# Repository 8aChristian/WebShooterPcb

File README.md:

# 🕸️ WebShooter — Wearable Actuation & High-Response Sensing PCB

<div align="center">

</div>

---

## 1. 🎯 Objective

**WebShooter** is a compact, high-reliability wearable controller PCB designed for rapid biosignal/force acquisition, low-latency electronic valve actuation, and external brushless motor ESC control.

Built around the **ESP32-C3 SuperMini** (RISC-V 32-bit architecture), the system is engineered to withstand intense inductive transients and severe electromagnetic interference (EMI) from high-power loads while providing precision analog readings from a Force Sensing Resistor (FSR).

> [!NOTE]
> **Key Capabilities:**
> - **Fast Response Time:** Sub-millisecond analog force detection via hardware RC filtering.
> - **Inductive Load Immunity:** High-speed Schottky flyback suppression and isolated ground return loops.
> - **Modular Design:** Socketed MCU mounting for effortless replacement and maintenance.

---

## 2. 🏗️ System Architecture

```mermaid
graph LR
    subgraph Power_Stage ["Power and Regulation Stage"]
        BATT["Battery LiPo 2S (7.4V - 8.4V)"] -->|J_BATT| LDO["AMS1117-3.3 LDO"]
        LDO -->|"10uF In + 22uF Out"| V33["3.3V DC Clean Rail"]
    end

    subgraph MCU_Stage ["Control Unit ESP32-C3 SuperMini"]
        V33 --> MCU["ESP32-C3 (RISC-V @ 160MHz)"]
        MCU -->|GPIO8| LED["Status Indicator LED"]
    end

    subgraph Sensor_Stage ["Analog Force Sensing"]
        V33 --> FSR_DIV["10k Ohm Reference Divider"]
        FSR["FSR402 Sensor"] --> FSR_DIV
        FSR_DIV -->|"100nF LowPass + 1k Ohm Prot"| ADC["GPIO0 (ADC1_CH0)"]
    end

    subgraph Actuation_Stage ["Power Actuation and Motor Drive"]
        MCU -->|GPIO7 Logic Gate| DRV["AO3400A N-MOSFET (30V / 5.7A)"]
        BATT -->|7.4V Heavy Rail| SOL["Solenoid Valve (Inductive Load)"]
        DRV -->|"Drain + SS14 Flyback Diode"| SOL
        MCU -->|"GPIO6 PWM - 100 Ohm Damper"| ESC["External ESC (SpeedX2 1404 BLDC)"]
        BATT -.->|"Direct Battery Wiring"| ESC
    end
```

- **MCU:** ESP32-C3 SuperMini (RISC-V 32-bit single-core @ 160 MHz, 400 KB SRAM, 4 MB Flash, Wi-Fi + BLE 5).
- **Analog Front-End (AFE):** Precision voltage divider with a 100 nF ceramic low-pass filter ($f_c \approx 159\text{ Hz}$) and $1\text{ k}\Omega$ series current limiter.
- **Power Management & Drive:** AMS1117-3.3 LDO regulator with dual ceramic filtering; logic-level AO3400A N-MOSFET with SS14 Schottky flyback protection; isolated ESC PWM signaling.

---

## 3. 🔬 Component Selection & Design Decisions

| Subsystem | Component Selected | Engineering Rationale & Justification |
| :--- | :--- | :--- |
| **Microcontroller** | **ESP32-C3 SuperMini** | Ultra-compact footprint ($22.5 \times 18\text{ mm}$), native 12-bit ADC, hardware PWM timers, low power consumption, and integrated 2.4 GHz Wi-Fi/BLE for wireless telemetry. Mounted on **2.54 mm female headers** (`J1`, `J2`) to prevent module thermal stress during assembly and allow instant replacement. |
| **Solenoid Driver** | **AO3400A N-MOSFET** (SOT-23) | Ultra-low on-resistance ($R_{DS(on)} < 33\text{ m}\Omega$ @ $V_{GS} = 2.5\text{V}$), fully saturated with the ESP32's 3.3V logic. At $I = 0.8\text{A}$, power dissipation is negligible ($P_{cond} \approx 21.1\text{ mW}$), eliminating the need for bulky heatsinks. |
| **Flyback Protection** | **SS14 Schottky Diode** (SOD-123) | Placed directly in antiparallel across the solenoid terminals. Ultrafast reverse recovery ($t_{rr} < 10\text{ ns}$) and $0.5\text{V}$ forward drop clamp inductive voltage spikes ($V = -L \frac{di}{dt}$) to protect the MOSFET drain and ground plane from EMI bursts. |
| **Voltage Regulator** | **AMS1117-3.3** (SOT-223) | Handles 7.4V–8.4V LiPo 2S input with 1A current capacity. SOT-223 tab is tied to the output plane for optimal thermal dissipation. Paired with $10\,\mu\text{F}$ input and $22\,\mu\text{F}$ output ceramic X7R capacitors. |
| **Force Sensor AFE** | **FSR402 Divider + RC Filter** | Converts pressure ($0.2\text{ N} - 20\text{ N}$) into a clean $0.03\text{V} - 3.0\text{V}$ voltage curve. The hardware RC filter ($10\text{ k}\Omega \parallel 100\text{ nF}$) removes mechanical contact bounce and EMI from nearby motor switching. |
| **Motor & ESC Isolation** | **Signal-Only PWM Interface** | Heavy motor currents (up to 15A from the SpeedX2 1404 BLDC) are powered **directly from the battery pack wiring harness**. Only the PWM control line and reference ground pass through the PCB, preventing ground bounce and motor hash from corrupting the ADC. |

---

## 4. 📐 Schematic Overview

<div align="center">
  
  <p><em>Full vector PDF schematic is available in the <a href="schematic/WebShooter_Schematic.pdf"><code>/schematic</code></a> folder.</em></p>
</div>

> [!TIP]
> **Complete Schematic Documentation:**
> - 📄 **PDF Format:** [`schematic/WebShooter_Schematic.pdf`](schematic/WebShooter_Schematic.pdf)
> - 🎨 **Vector SVG:** [`schematic/WebShooter_Schematic.svg/`](schematic/WebShooter_Schematic.svg/)
> - 💻 **KiCad Source:** [`pcb/WebShooter.kicad_sch`](pcb/WebShooter.kicad_sch)

---

## 5. 🖨️ PCB Layout & Routing Strategy

<div align="center">

| Top Layer 2D Layout (F.Cu) | Bottom Layer 2D Layout (B.Cu) |
| :---: | :---: |
|  |  |

| 3D Render - Top Side | 3D Render - Bottom Side |
| :---: | :---: |
|  |  |

</div>

### 🛠️ Layer Stackup & Dimensions
- **Layer Count:** 2-Layer FR4 ($1.6\text{ mm}$ board thickness, $1\text{ oz} / 35\,\mu\text{m}$ copper weight).
- **Board Dimensions:** $38.0\text{ mm} \times 38.0\text{ mm}$ with $2.0\text{ mm}$ corner radius fillets (Ultra-compact wearable standard).
- **Mounting Hole Grid:** 4x M2 mounting holes on a $31.0 \times 31.0\text{ mm}$ pattern ($3.5\text{ mm}$ from board edges).

### 📐 Routing Guidelines & DFM Standards Applied
1. **Strict 45° Mitered Routing (Zero 90° Corners):**
   - All track bends utilize **45-degree chamfers** or smooth radii.
   - *Why:* Eliminates **acid traps** during chemical etching in fab, avoids acute impedance steps, and prevents solder mask delamination.
2. **Edge Pullback Clearance ($\ge 1.0\text{ mm}$):**
   - All copper tracks, vias, and copper pour zones maintain at least **$1.0\text{ mm}$ of clearance** from the `Edge_Cuts` perimeter.
   - *Why:* Prevents copper shearing, burrs, and shorts during CNC V-scoring and board routing.
3. **Trace Width Dimensioning (IPC-2152):**
   - **Power & Solenoid Traces:** $1.0\text{ mm} - 1.2\text{ mm}$ (Handles up to $3\text{A}$ continuous with $\Delta T < 10^\circ\text{C}$).
   - **3.3V Power Distribution:** $0.8\text{ mm}$.
   - **Digital PWM & Analog Signals:** $0.35\text{ mm} - 0.40\text{ mm}$.
4. **Dual Continuous Ground Planes:**
   - Both `F.Cu` and `B.Cu` feature unbroken GND copper zones connected through thermal reliefs (`ZONE_CONNECTION_THERMAL`) on all through-hole and SMD ground pins.

---

## 6. ✅ DRC & Quality Verification

Automated Design Rule Check (DRC) executed via `kicad-cli`:

```text
** KiCad 10 Design Rule Check Report **
Project: WebShooter.kicad_pcb
Date: 2026-08-20

[+] Status: PASSED
[+] Total DRC Violations: 0
[+] Unconnected Elements: 0
[+] Footprint Courtyard Overlaps: 0
[+] Solder Mask Bridges: 0
[+] Silk Over Exposure: 0
```

> [!IMPORTANT]
> The full verification report is saved in [`pcb/WebShooter-drc.rpt`](pcb/WebShooter-drc.rpt).

---

## 7. 🧊 3D Model & Mechanical Integration

- **PCB 3D Model:** Ready-to-import STEP file:
  - 📁 [`3d-model/WebShooter.step`](3d-model/WebShooter.step)
- **Wearable Case / Enclosure (CAD):** Parametric wrist case model for 3D printing:
  - 📦 [`3d-model/WEBSHOOTERCASEFINAL.f3d`](3d-model/WEBSHOOTERCASEFINAL.f3d) (Autodesk Fusion 360 source archive)
- **Mechanical Mounting:** 4x M2 mounting holes on a $31.0 \times 31.0\text{ mm}$ square grid ($3.5\text{ mm}$ edge offset), designed to mate directly with the 3D-printed enclosure standoffs.

---

## 8. 🏭 Manufacturing & Assembly (JLCPCB / PCBWay Ready)

| Asset | Location / File | Purpose |
| :--- | :--- | :--- |
| **Gerber Files (ZIP)** | [`gerbers/WebShooter_Gerbers_JLCPCB.zip`](gerbers/WebShooter_Gerbers_JLCPCB.zip) | One-click drag-and-drop file for instant online quoting |
| **Individual Gerbers** | [`gerbers/`](gerbers/) | Standard RS-274X layers (`.gtl`, `.gbl`, `.gts`, `.gbs`, `.gto`, `.gm1`...) |
| **Drill File** | [`gerbers/WebShooter.drl`](gerbers/WebShooter.drl) | Excellon CNC drill specifications |
| **BOM (CSV)** | [`bom/WebShooter_BOM.csv`](bom/WebShooter_BOM.csv) | Component spreadsheet with LCSC Part Numbers |
| **BOM (Markdown)** | [`bom/WebShooter_BOM.md`](bom/WebShooter_BOM.md) | Formatted Bill of Materials table |
| **Case CAD (F3D)** | [`3d-model/WEBSHOOTERCASEFINAL.f3d`](3d-model/WEBSHOOTERCASEFINAL.f3d) | 3D-printable parametric enclosure design |

### 🚀 Production Parameters Recommended
- **Base Material:** FR-4 (Tg 130–140°C).
- **PCB Thickness:** 1.6 mm.
- **Copper Weight:** 1 oz ($35\,\mu\text{m}$).
- **Surface Finish:** HASL Lead-Free or ENIG (Electroless Nickel Immersion Gold).
- **Solder Mask:** Matte Black / Blue / Green.
- **Silkscreen:** High-contrast White.

---

## 📜 License

This project is licensed under the [MIT License](LICENSE) — Feel free to use, modify, and manufacture this board for open-source and commercial hardware projects.

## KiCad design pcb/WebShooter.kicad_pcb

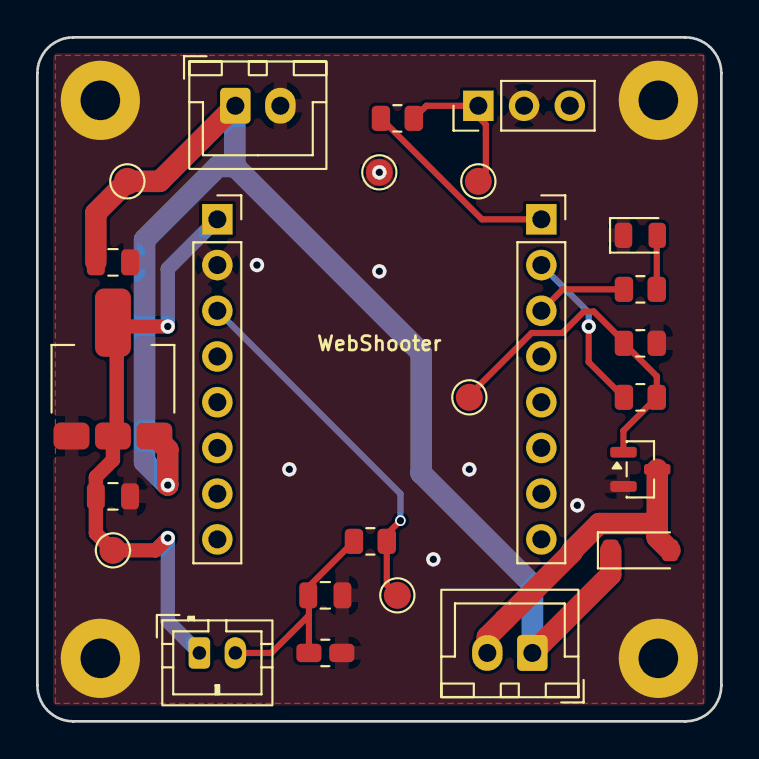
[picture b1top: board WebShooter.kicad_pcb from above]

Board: 2 copper layers, 38.0 x 38.0 mm, 29 parts (0 on the bottom side), 12 nets.

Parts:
C_FILT: 100nF; C_0805_2012Metric
C_IN: 10uF; C_0805_2012Metric
C_OUT: 22uF; C_0805_2012Metric
D1: SS14; D_SOD-123
D2: LED_STAT; LED_0805_2012Metric
H1, H2, H3, H4: MountingHole_2.2mm_M2_Pad
J1: ESP32_LEFT; PinSocket_1x08_P2.54mm_Vertical
J2: ESP32_RIGHT; PinSocket_1x08_P2.54mm_Vertical
J_BATT: BATT_2S; JST_XH_B2B-XH-A_1x02_P2.50mm_Vertical
J_ESC: ESC_SIG; PinHeader_1x03_P2.54mm_Vertical
J_FSR: FSR_SENSOR; JST_PH_B2B-PH-K_1x02_P2.00mm_Vertical
J_SOL: SOLENOID; JST_XH_B2B-XH-A_1x02_P2.50mm_Vertical
Q1: AO3400A; SOT-23
R_G: 100; R_0805_2012Metric
R_LED: 1k; R_0805_2012Metric
R_PD: 10k; R_0805_2012Metric
R_PROT: 1k; R_0805_2012Metric
R_PWM: 100; R_0805_2012Metric
R_REF: 10k; R_0805_2012Metric
TP_3V3: TP_3V3; TestPoint_Pad_D1.5mm
TP_ESC: TP_ESC; TestPoint_Pad_D1.5mm
TP_FSR: TP_FSR; TestPoint_Pad_D1.5mm
TP_GATE: TP_GATE; TestPoint_Pad_D1.5mm
TP_GND: TP_GND; TestPoint_Pad_D1.5mm
TP_VBATT: TP_VBATT; TestPoint_Pad_D1.5mm
U1: AMS1117-3.3; SOT-223-3_TabPin2

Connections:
+3.3V: C_OUT.1, J1.1, J_FSR.1, TP_3V3.1, U1.2
+BATT: C_IN.1, D1.1, J_BATT.1, J_SOL.1, TP_VBATT.1, U1.3
ESC_PWM: J_ESC.1, R_PWM.2, TP_ESC.1
FSR_ADC: J1.3, R_PROT.2, TP_FSR.1
FSR_IN: C_FILT.1, J_FSR.2, R_PROT.1, R_REF.1
GND: C_FILT.2, C_IN.2, C_OUT.2, D2.1, H1.1, H2.1, H3.1, H4.1, J1.2, J_BATT.2, J_ESC.2, Q1.2, R_PD.2, R_REF.2, TP_GND.1, U1.1
LED_A: D2.2, R_LED.2
LED_STAT: J2.3, R_LED.1
MCU_GATE: J2.2, R_G.1
MCU_PWM: J2.1, R_PWM.1
SOL_DRAIN: D1.2, J_SOL.2, Q1.3
SOL_GATE: Q1.1, R_G.2, R_PD.1, TP_GATE.1

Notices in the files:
README.md:
License: MIT
